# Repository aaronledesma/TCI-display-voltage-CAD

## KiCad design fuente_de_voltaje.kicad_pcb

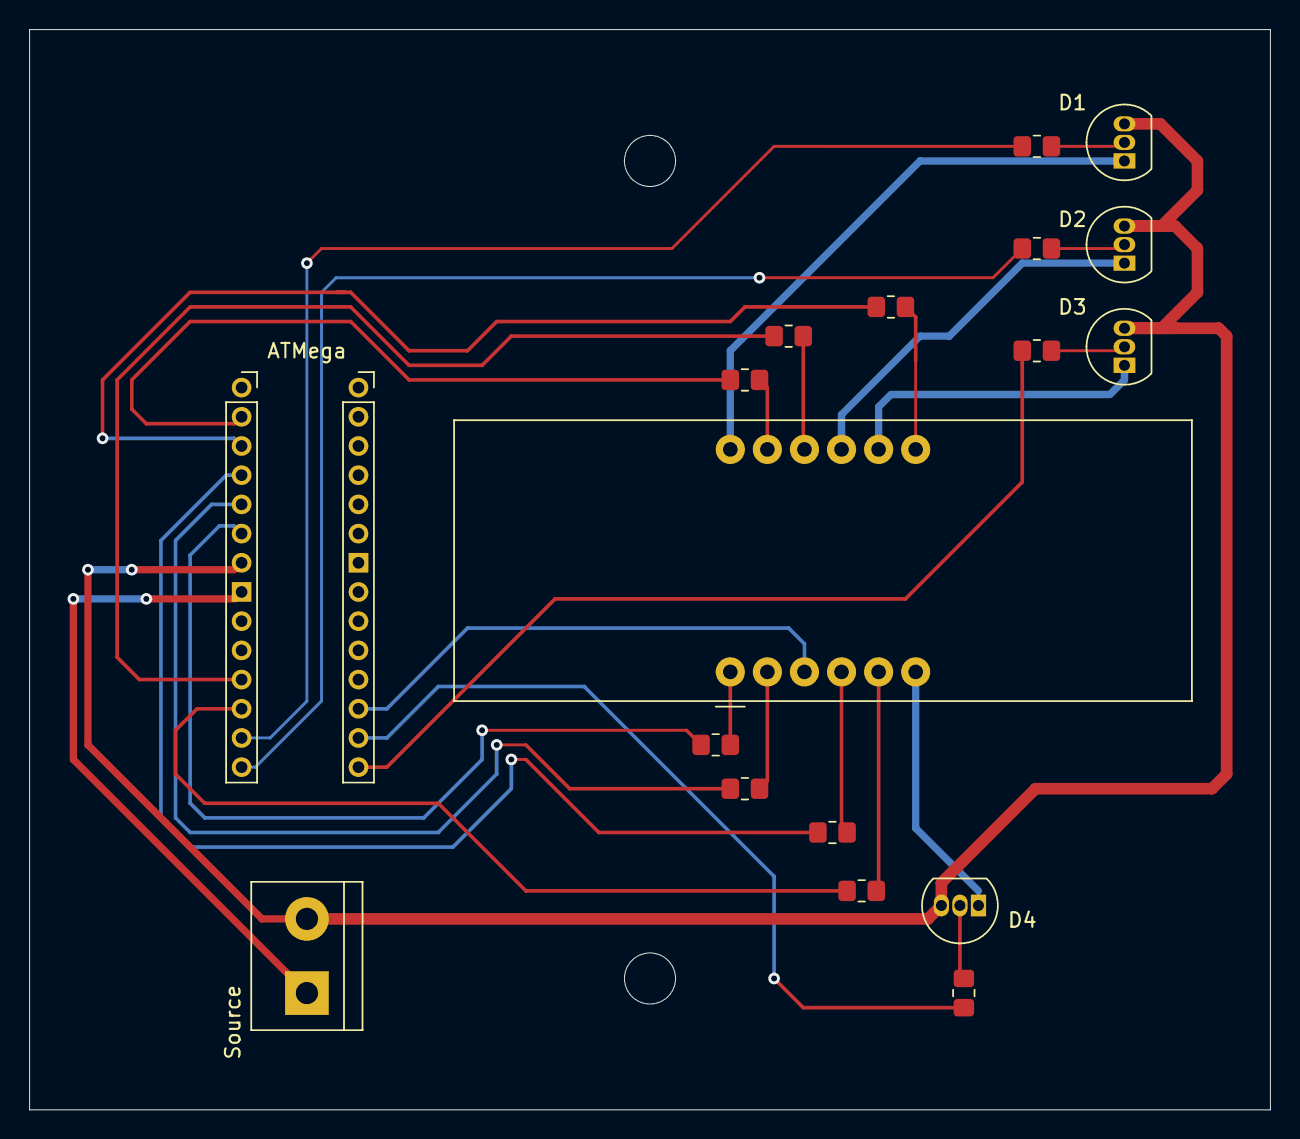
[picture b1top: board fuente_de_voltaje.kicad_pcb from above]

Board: 2 copper layers, 85.0 x 74.0 mm, 19 parts (0 on the bottom side), 28 nets.

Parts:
D1, D2, D3, D4: 2N3904; TO-92_Inline
J1, J2: Conn_01x14; PinSocket_1x14_P2.00mm_Vertical
R1, R2, R3, R4, R5, R6, R7: 330; R_0805_2012Metric_Pad1.20x1.40mm_HandSolder
R8, R9, R10, R11: 1k; R_0805_2012Metric_Pad1.20x1.40mm_HandSolder
Source: TerminalBlock_bornier-2_P5.08mm
U1: CC56-12SURKWA; CA56-12SURKWA

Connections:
unnamed: D1.3, D2.3, D3.3, D4.3, J1.7, Source.2
unnamed: J1.8, Source.1
unnamed: J1.13, R10.1
unnamed: J1.14, R8.1
unnamed: D3.2, R11.1
unnamed: D4.2, R9.1
unnamed: R1.1, U1.11
unnamed: R2.1, U1.7
unnamed: R3.1, U1.4
unnamed: R4.1, U1.2
unnamed: R5.1, U1.1
unnamed: R6.1, U1.10
unnamed: R7.1, U1.5
unnamed: D2.2, R8.2
unnamed: J2.16, R9.2
unnamed: D1.2, R10.2
unnamed: J2.17, U1.3
unnamed: D4.1, U1.6
unnamed: D3.1, U1.8
unnamed: D2.1, U1.9
unnamed: D1.1, U1.12
a: J1.2, R1.2
b: J1.3, R2.2
c: J1.4, R3.2
d: J1.5, R4.2
e: J1.6, R5.2
f: J1.11, R6.2
g: J1.12, R7.2

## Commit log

2021-11-27 primera subida
